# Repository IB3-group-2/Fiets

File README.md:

# Fiets

https://discord.gg/eE4hEDwp

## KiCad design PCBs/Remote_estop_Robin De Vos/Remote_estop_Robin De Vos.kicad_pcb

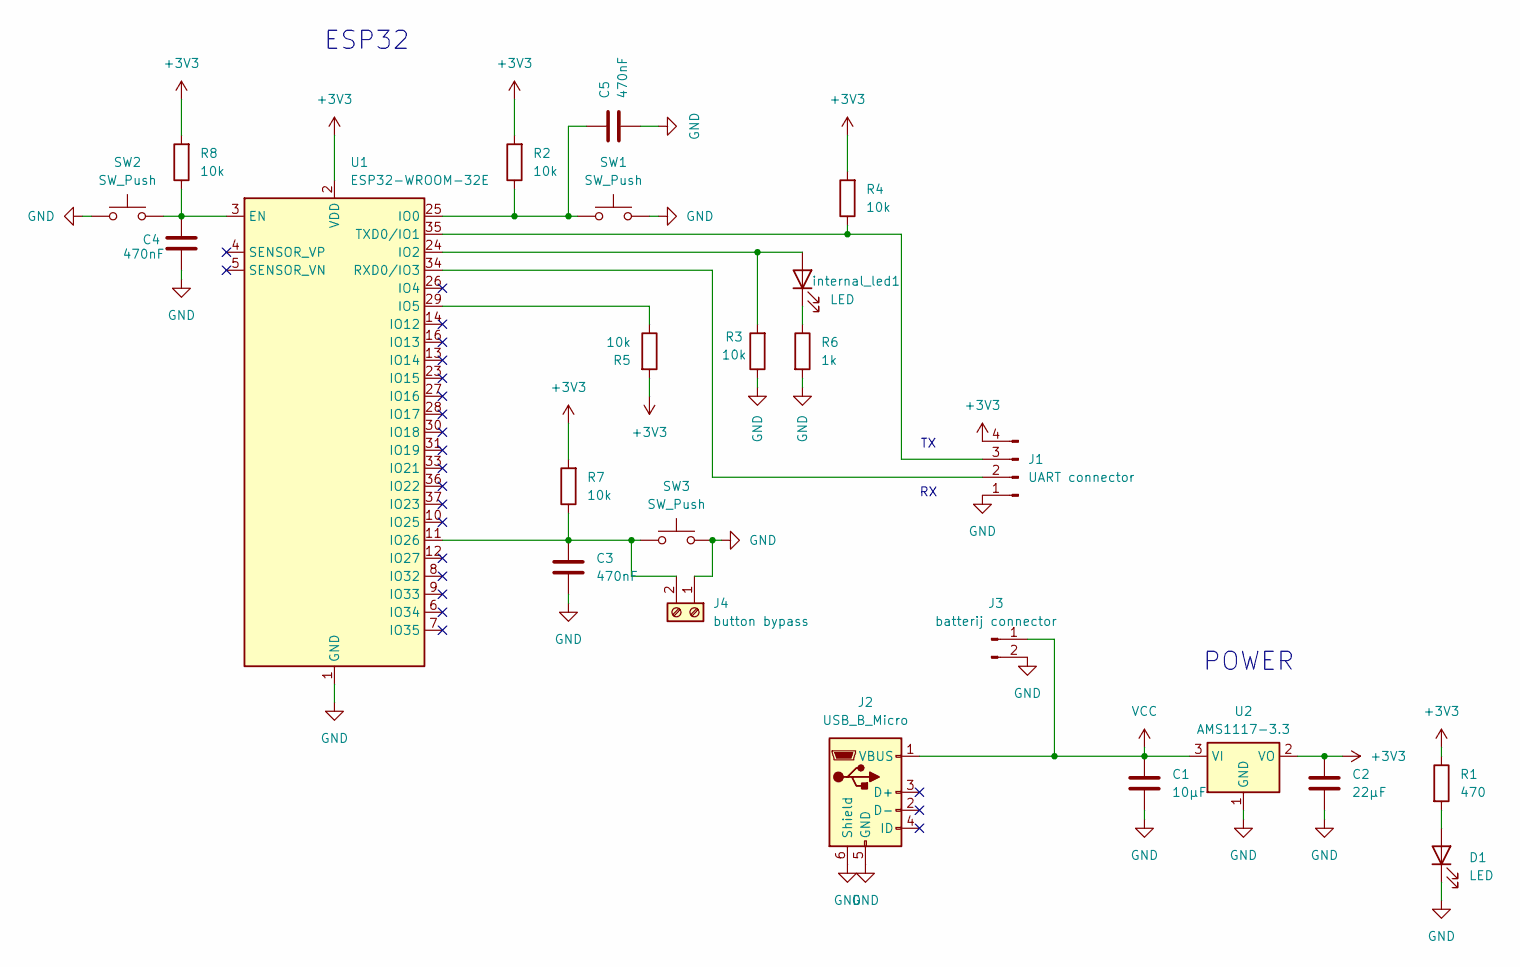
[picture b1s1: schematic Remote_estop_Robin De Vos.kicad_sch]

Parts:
C1: 10µF; C_0805_2012Metric_Pad1.18x1.45mm_HandSolder
C2: 22µF; C_0805_2012Metric_Pad1.18x1.45mm_HandSolder
C3, C4, C5: 470nF; C_0805_2012Metric_Pad1.18x1.45mm_HandSolder
D1: LED; LED_0805_2012Metric_Pad1.15x1.40mm_HandSolder
J1: UART connector; PinHeader_1x04_P2.54mm_Vertical
J2: USB_B_Micro; USB_Micro-B_Molex-105017-0001
J3: batterij connector; PinHeader_1x02_P2.54mm_Vertical
J4: button bypass; TerminalBlock_MaiXu_MX126-5.0-02P_1x02_P5.00mm
R1: 470; R_0805_2012Metric_Pad1.20x1.40mm_HandSolder
R2, R3, R4, R5, R7, R8: 10k; R_0805_2012Metric_Pad1.20x1.40mm_HandSolder
R6: 1k; R_0805_2012Metric_Pad1.20x1.40mm_HandSolder
SW1, SW2, SW3: SW_Push; 434111043826
U1: ESP32-WROOM-32E; ESP32-WROOM-32D
U2: AMS1117-3.3; SOT-223-3_TabPin2
internal_led1: LED; LED_0805_2012Metric_Pad1.15x1.40mm_HandSolder

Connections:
+3V3: C2.1, J1.4, R1.1, R2.2, R4.2, R5.2, R7.2, R8.2, U1.2 (VDD), U2.2 (VO)
GND: C1.2, C2.2, C3.2, C4.2, C5.2, D1.1 (K), J1.1, J2.5 (GND), J2.6 (Shield), J3.2, J4.1, R3.1, R6.2, SW1.2, SW2.1, SW3.2, U1.1 (GND), U1.15 (GND), U1.38 (GND), U1.39 (GND), U2.1 (GND)
unnamed: D1.2 (A), R1.2
unnamed: J1.2, U1.34 (RXD0/IO3)
unnamed: J1.3, R4.1, U1.35 (TXD0/IO1)
unnamed: C3.1, J4.2, R7.1, SW3.1, U1.11 (IO26)
unnamed: C4.1, R8.1, SW2.2, U1.3 (EN)
unnamed: C5.1, R2.1, SW1.1, U1.25 (IO0)
unnamed 8: R3.2, U1.24 (IO2), internal_led1.2 (A); also elsewhere on the board
unnamed: R5.1, U1.29 (IO5)
unnamed 10: R6.1, internal_led1.1 (K); also elsewhere on the board
VCC: C1.1, J2.1 (VBUS), J3.1, U2.3 (VI)

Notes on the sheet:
POWER
ESP32

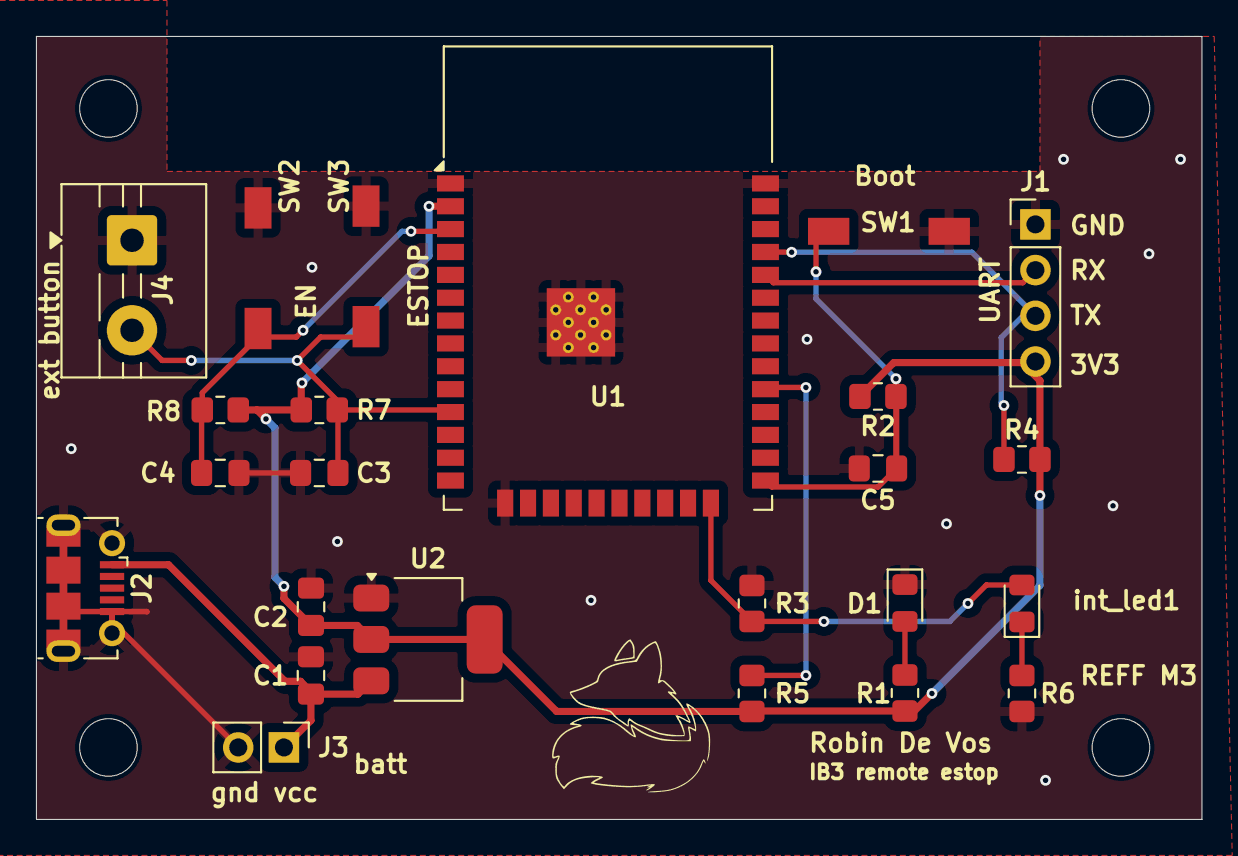
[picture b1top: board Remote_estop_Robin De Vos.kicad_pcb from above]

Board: 2 copper layers, 64.8 x 43.5 mm, 25 parts (0 on the bottom side), 12 nets.

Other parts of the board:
REFF M3: MountingHole_3.2mm_M3
int_led1: LED; LED_0805_2012Metric_Pad1.15x1.40mm_HandSolder

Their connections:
unnamed 8: int_led1.2 (A); also elsewhere on the board
unnamed 10: int_led1.1 (K); also elsewhere on the board

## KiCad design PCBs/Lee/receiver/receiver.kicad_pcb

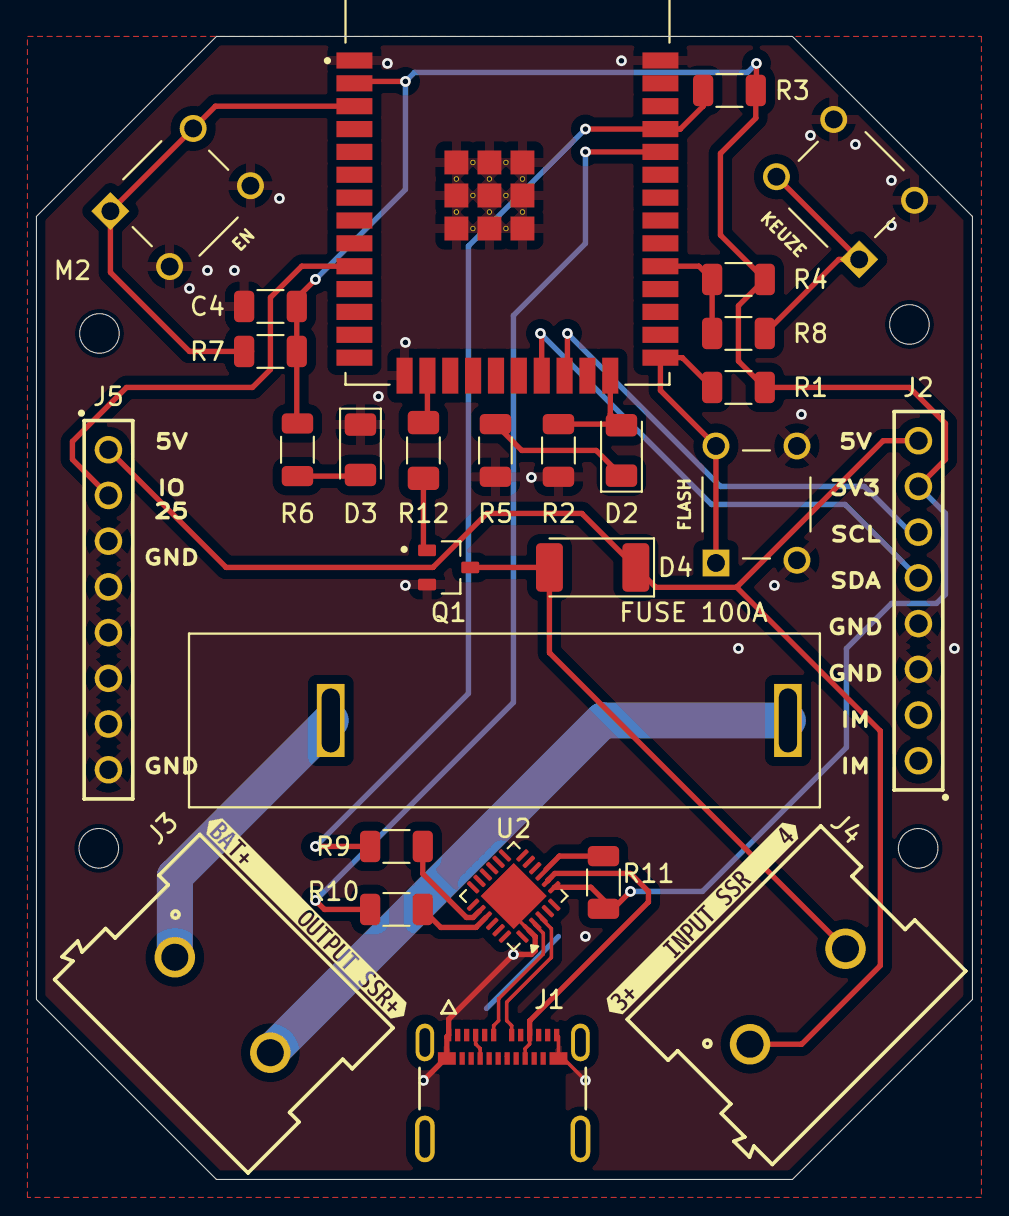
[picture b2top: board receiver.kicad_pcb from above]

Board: 2 copper layers, 52.0 x 63.5 mm, 34 parts (0 on the bottom side), 27 nets.

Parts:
C4: 100uF/6.3V; R_1206_3216Metric
D2: BLUE; LED_1206_3216Metric
D3: RED; LED_1206_3216Metric
D4: SM4007; D_MELF
EN: 3-1825910-1; TE_3-1825910-1
FLASH: 3-1825910-1; TE_3-1825910-1
FUSE 100A: Fuseholder; FUSE_3526
H2, H3, H4: MountingHole; MountingHole_2.2mm_M2
J1: 1054500101 USB-C; MOLEX_1054500101
J2: Ingangspinnen; 61300811821
J3: J3; 691253910002
J4: INPUT SSR; 691253910002
J5: motorcontroller; 61300811821
KEUZE: 3-1825910-1; TE_3-1825910-1
M2: MountingHole; MountingHole_2.2mm_M2
Q1: BC847A; TRANS_BC847A
R1, R2, R3, R4: 10k; R_1206_3216Metric
R5, R6, R9, R10: 1k; R_1206_3216Metric
R7: 10K; R_1206_3216Metric
R8: 200; R_1206_3216Metric
R11: 4.7k; R_1206_3216Metric
R12: 1k; R_1206_3216Metric_Pad1.30x1.75mm_HandSolder
U1: ESP32-WROOM-32; MODULE_ESP32-WROOM-32
U2: CP2102N; QFN-24-1EP_4x4mm_P0.5mm_EP2.6x2.6mm
kibuzzard-69131E5B: G***; kibuzzard-69131E5B
kibuzzard-69131EBA: G***; kibuzzard-69131EBA

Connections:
5V: D4.1 (K), J2.8, J4.1, J5.1
/BAT +: FUSE 100A.1, J3.1
/INPUT SSR 4: D4.2 (A), J4.2, Q1.3
/OUTPUT SSR +: FUSE 100A.2, J3.2
D+: J1.A6 (D1+), U2.3 (D+)
D-: J1.A7 (D1-), U2.4 (D-)
EN: EN.1, EN.2, R7.2, U1.3 (EN)
GND: C4.2, D3.1 (K), EN.3, EN.4, FLASH.3, FLASH.4, J1.A1 (GND_A1), J1.A12 (GND_A12), J1.B1 (GND_B1), J1.B12 (GND_B12), J2.3, J2.4, J5.3, J5.4, J5.5, J5.6, J5.7, J5.8, KEUZE.3, KEUZE.4, Q1.2, R2.1, R5.2, U1.1 (GND), U1.15 (GND), U1.38 (GND), U1.39_1 (GND), U1.39_2 (GND), U1.39_3 (GND), U1.39_4 (GND), U1.39_5 (GND), U1.39_6 (GND), U1.39_7 (GND), U1.39_8 (GND), U1.39_9 (GND), U1.39_10 (GND), U1.39_11 (GND), U1.39_12 (GND), U1.39_13 (GND), U1.39_14 (GND), U1.39_15 (GND), U1.39_16 (GND), U1.39_17 (GND), U1.39_18 (GND), U1.39_19 (GND), U1.39_20 (GND), U1.39_21 (GND), U2.2 (GND), U2.25 (GND)
GPIO0: FLASH.1, FLASH.2, R1.2, U1.25 (IO0)
GPIO2: D2.2 (A), R2.2, U1.24 (IO2)
GPIO5: R4.2, R8.1, U1.29 (IO5)
GPIO13: R12.1, U1.16 (IO13)
GPIO25: J5.2, U1.10 (IO25)
Imeasure: J2.1, J2.2
unnamed: D2.1 (K), R5.1
unnamed: D3.2 (A), R6.2
unnamed: KEUZE.1, KEUZE.2, R8.2
unnamed: Q1.1, R12.2
unnamed: R9.1, U2.20 (RXD)
unnamed: R10.1, U2.21 (TXD)
unnamed: R11.2, U2.9 (~RST)
RX0: R10.2, U1.34 (RXD0)
SCL: J2.6, U1.22 (SDI/SD1)
SDA: J2.5, U1.21 (SDO/SD0)
TX0: R3.2, R9.2, U1.35 (TXD0)
VCCUSB: J1.A4 (VBUS_A4), J1.A9 (VBUS_A9), J1.B4 (VBUS_B4), J1.B9 (VBUS_B9), U2.8 (VBUS)
VDD3V3: C4.1, J2.7, R1.1, R3.1, R4.1, R6.1, R7.1, R11.1, U1.2 (3V3), U2.6 (VDD), U2.7 (VREGIN)

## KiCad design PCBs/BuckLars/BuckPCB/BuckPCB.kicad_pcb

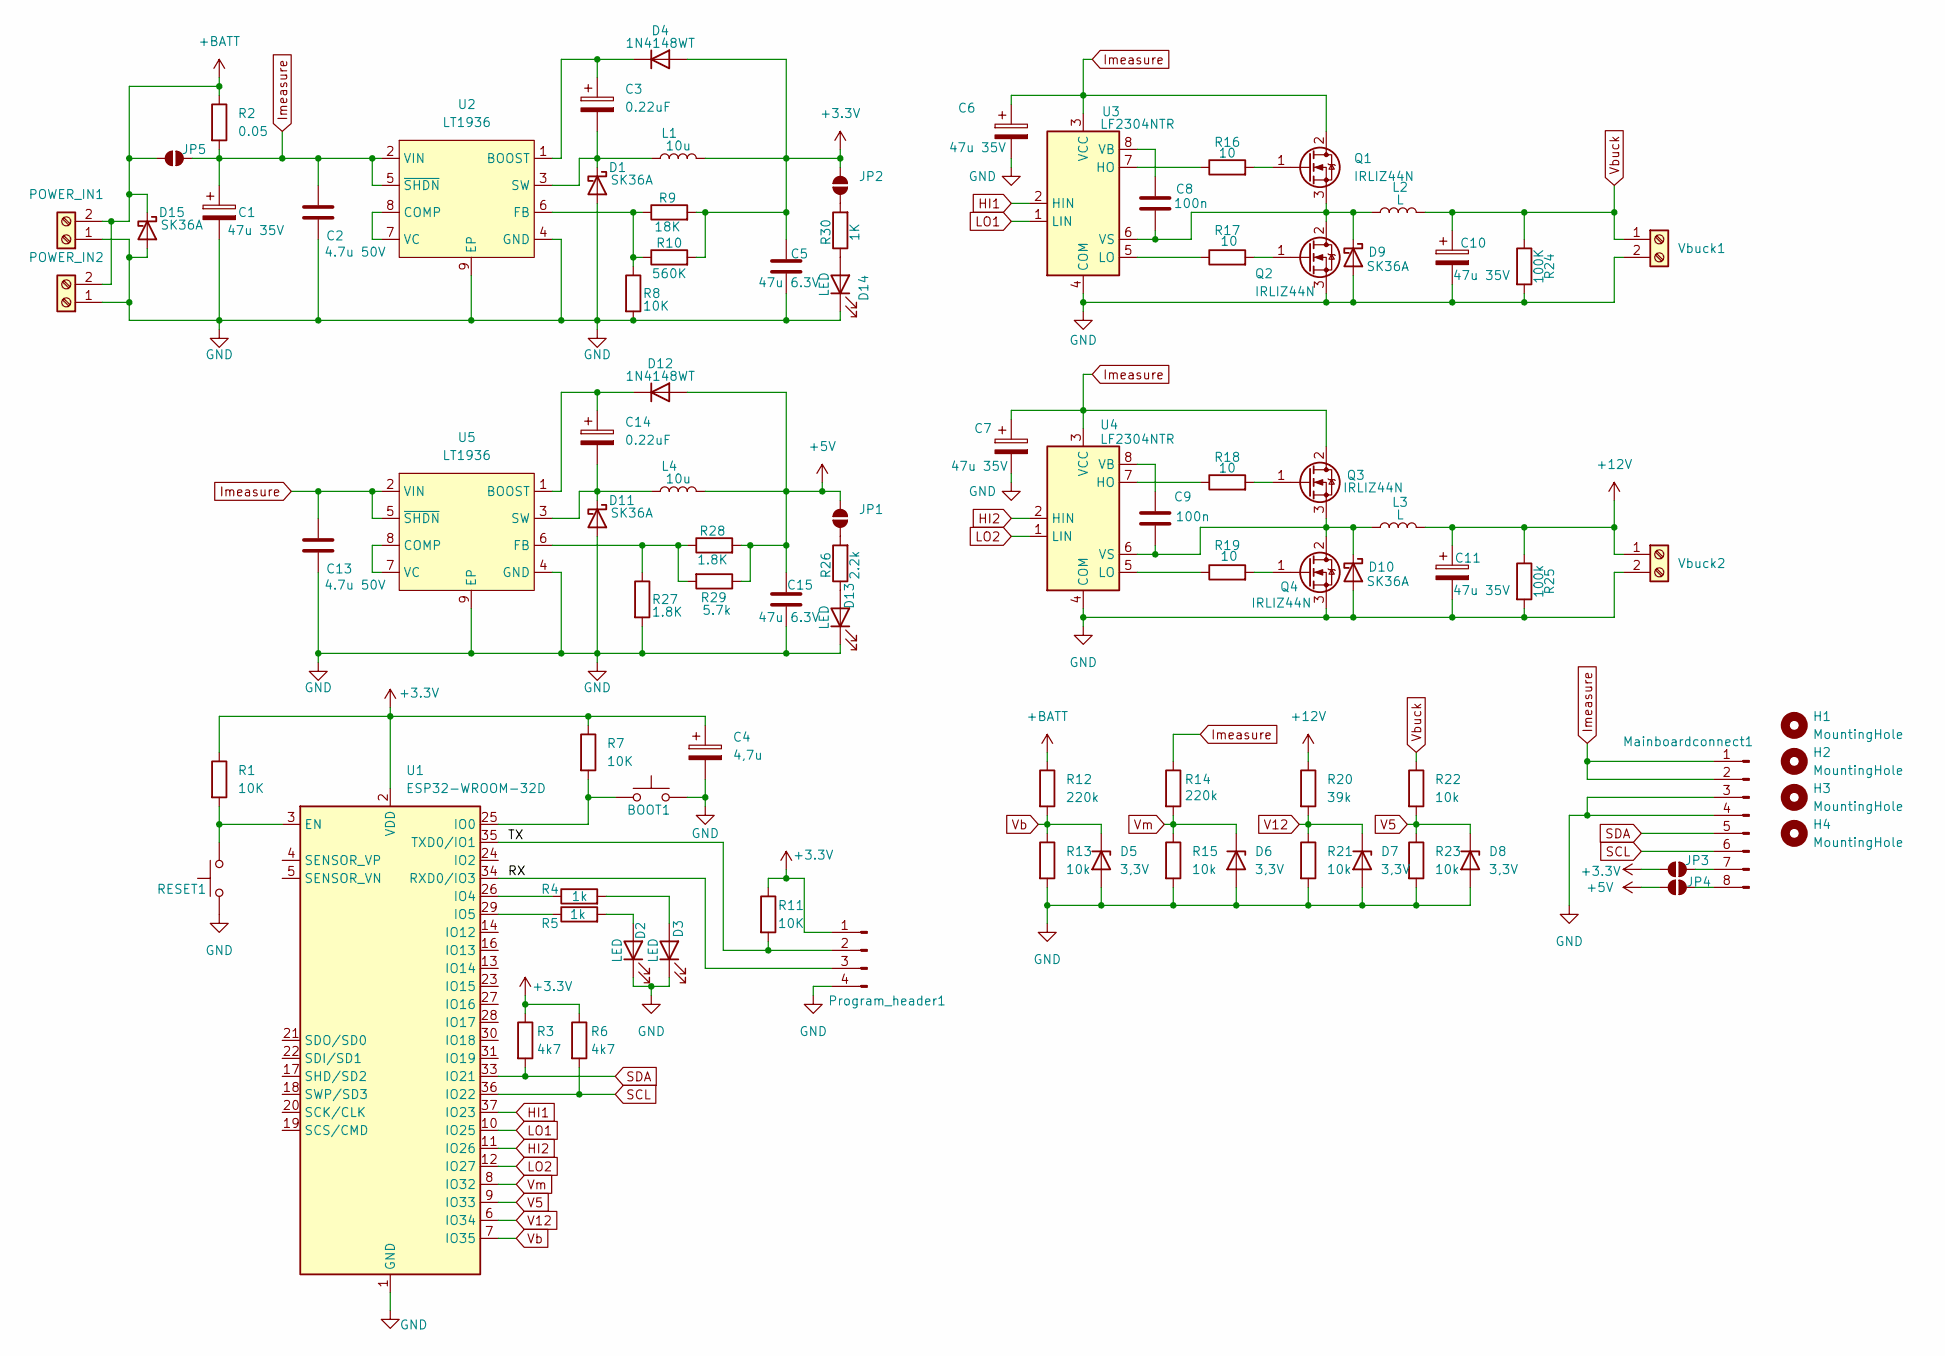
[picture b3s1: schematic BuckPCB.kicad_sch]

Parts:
BOOT1: BOOT; SW_Tactile_SPST_NO_Straight_CK_PTS636Sx25SMTRLFS
C1, C6, C7, C10, C11: 47u 35V; CP_Elec_6.3x5.7
C2, C13: 4.7u 50V; D_1206_3216Metric_Pad1.42x1.75mm_HandSolder
C3, C14: 0.22uF; C_1206_3216Metric_Pad1.33x1.80mm_HandSolder
C4: 4,7u; CP_Elec_4x5.3
C5, C15: 47u 6.3V; D_1206_3216Metric_Pad1.42x1.75mm_HandSolder
C8, C9: 100n; C_1206_3216Metric_Pad1.33x1.80mm_HandSolder
D1, D9, D10, D11, D15: SK36A; D_SMC-RM10_Universal_Handsoldering
D2, D3, D13, D14: LED; LED_0805_2012Metric
D4, D12: 1N4148WT; D_SOD-523
D5, D6, D7, D8: 3,3V; D_1206_3216Metric
H1, H2, H3, H4: MountingHole; MountingHole_3.2mm_M3_ISO14580
JP1, JP2, JP3, JP4, JP5: SolderJumper_2_Open; SolderJumper-2_P1.3mm_Open_TrianglePad1.0x1.5mm
L1, L4: 10u; L_7.3x7.3_H4.5
L2, L3: L; L_7.3x7.3_H4.5
Mainboardconnect1: Conn_01x08_Pin; PinHeader_1x08_P2.54mm_Vertical
POWER_IN1, POWER_IN2: POWER_IN; TerminalBlock_MaiXu_MX126-5.0-02P_1x02_P5.00mm
Program_header1: Program_header; PinHeader_1x04_P2.54mm_Vertical
Q1, Q2, Q3, Q4: IRLIZ44N; TO-220F-3_Vertical
R1, R7, R8, R11: 10K; R_1206_3216Metric_Pad1.30x1.75mm_HandSolder
R2: 0.05; R_4020_10251Metric_Pad1.65x5.30mm_HandSolder
R3, R6: 4k7; R_1206_3216Metric_Pad1.30x1.75mm_HandSolder
R4, R5: 1k; R_1206_3216Metric_Pad1.30x1.75mm_HandSolder
R9: 18K; R_1206_3216Metric_Pad1.30x1.75mm_HandSolder
R10: 560K; R_1206_3216Metric_Pad1.30x1.75mm_HandSolder
R12, R14: 220k; R_1206_3216Metric_Pad1.30x1.75mm_HandSolder
R13, R15, R21, R22, R23: 10k; R_1206_3216Metric_Pad1.30x1.75mm_HandSolder
R16, R17, R18, R19: 10; R_1206_3216Metric_Pad1.30x1.75mm_HandSolder
R20: 39k; R_1206_3216Metric_Pad1.30x1.75mm_HandSolder
R24: 100K; R_1206_3216Metric_Pad1.30x1.75mm_HandSolder
R25: 100k; R_1206_3216Metric_Pad1.30x1.75mm_HandSolder
R26: 2.2k; R_1206_3216Metric_Pad1.30x1.75mm_HandSolder
R27, R28: 1.8K; R_1206_3216Metric_Pad1.30x1.75mm_HandSolder
R29: 5.7k; R_1206_3216Metric_Pad1.30x1.75mm_HandSolder
R30: 1K; R_1206_3216Metric_Pad1.30x1.75mm_HandSolder
RESET1: RESET; SW_Tactile_SPST_NO_Straight_CK_PTS636Sx25SMTRLFS
U1: ESP32-WROOM-32D
U2, U5: LT1936; MSOP-8-1EP_3x3mm_P0.65mm_EP1.95x2.15mm
U3, U4: LF2304NTR; SOIC-8_3.9x4.9mm_P1.27mm
Vbuck1: Vbuck; TerminalBlock_MaiXu_MX126-5.0-02P_1x02_P5.00mm
Vbuck2: 12V; TerminalBlock_MaiXu_MX126-5.0-02P_1x02_P5.00mm

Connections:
+3.3V: C4.1, C5.1, D4.2 (A), JP2.2 (B), JP3.2 (B), L1.2, Program_header1.1, R1.1, R3.1, R6.1, R7.1, R9.2, R10.2, R11.1, U1.2 (VDD)
+5V: C15.1, D12.2 (A), JP1.2 (B), JP4.2 (B), L4.2, R28.2, R29.1
+12V: C11.1, L3.2, R20.1, R25.1, Vbuck2.1
+BATT: D15.1 (K), JP5.2 (B), POWER_IN1.2, POWER_IN2.2, R2.1, R12.1; also elsewhere on the board
/RX: Program_header1.3, U1.34 (RXD0/IO3)
/TX: Program_header1.2, R11.2, U1.35 (TXD0/IO1)
GND: BOOT1.2 (B), C1.2, C2.2, C4.2, C5.2, C6.2, C7.2, C10.2, C11.2, C13.2, C15.2, D1.2 (A), D2.1 (K), D3.1 (K), D5.2 (A), D6.2 (A), D7.2 (A), D8.2 (A), D9.2 (A), D10.2 (A), D11.2 (A), D13.1 (K), D14.1 (K), D15.2 (A), Mainboardconnect1.3, Mainboardconnect1.4, POWER_IN1.1, POWER_IN2.1, Program_header1.4, Q2.3 (S), Q4.3 (S), R8.2, R13.2, R15.2, R21.2, R23.2, R24.2, R25.2, R27.2, RESET1.1 (A), U1.1 (GND), U1.15 (GND), U1.38 (GND), U1.39 (GND), U2.4 (GND), U2.9 (EP), U3.4 (COM), U4.4 (COM), U5.4 (GND), U5.9 (EP), Vbuck1.2, Vbuck2.2
HI1: U1.37 (IO23), U3.2 (HIN)
HI2: U1.11 (IO26), U4.2 (HIN)
Imeasure: C1.1, C2.1, C6.1, C7.1, C13.1, JP5.1 (A), Mainboardconnect1.1, Mainboardconnect1.2, Q1.2 (D), Q3.2 (D), R2.2, R14.1, U2.2 (VIN), U2.5 (~SHDN), U3.3 (VCC), U4.3 (VCC), U5.2 (VIN), U5.5 (~SHDN); also elsewhere on the board
LO1: U1.10 (IO25), U3.1 (LIN)
LO2: U1.12 (IO27), U4.1 (LIN)
unnamed: BOOT1.1 (A), R7.2, U1.25 (IO0)
unnamed: C3.2, D1.1 (K), L1.1, U2.3 (SW)
unnamed: D2.2 (A), R5.2
unnamed: D3.2 (A), R4.2
unnamed: C3.1, D4.1 (K), U2.1 (BOOST)
unnamed: C8.2, D9.1 (K), L2.1, Q1.3 (S), Q2.2 (D), U3.6 (VS)
unnamed: C9.2, D10.1 (K), L3.1, Q3.3 (S), Q4.2 (D), U4.6 (VS)
unnamed: C14.2, D11.1 (K), L4.1, U5.3 (SW)
unnamed: C14.1, D12.1 (K), U5.1 (BOOST)
unnamed: D13.2 (A), R26.1
unnamed: D14.2 (A), R30.1
unnamed: JP1.1 (A), R26.2
unnamed: JP2.1 (A), R30.2
unnamed: JP3.1 (A), Mainboardconnect1.7
unnamed: JP4.1 (A), Mainboardconnect1.8
unnamed: Q1.1 (G), R16.2
unnamed: Q2.1 (G), R17.2
unnamed: Q3.1 (G), R18.2
unnamed: Q4.1 (G), R19.2
unnamed: R1.2, RESET1.2 (B), U1.3 (EN)
unnamed: R4.1, U1.26 (IO4)
unnamed: R5.1, U1.29 (IO5)
unnamed: U2.7 (VC), U2.8 (COMP)
unnamed: R8.1, R9.1, R10.1, U2.6 (FB)
unnamed: R16.1, U3.7 (HO)
unnamed: R17.1, U3.5 (LO)
unnamed: C8.1, U3.8 (VB)
unnamed: R18.1, U4.7 (HO)
unnamed: R19.1, U4.5 (LO)
unnamed: C9.1, U4.8 (VB)
unnamed: U5.7 (VC), U5.8 (COMP)
unnamed: R27.1, R28.1, R29.2, U5.6 (FB)
SCL: Mainboardconnect1.6, R6.2, U1.36 (IO22)
SDA: Mainboardconnect1.5, R3.2, U1.33 (IO21)
V5: D8.1 (K), R22.2, R23.1, U1.9 (IO33)
V12: D7.1 (K), R20.2, R21.1, U1.6 (IO34)
Vb: D5.1 (K), R12.2, R13.1, U1.7 (IO35)
Vbuck: C10.1, L2.2, R22.1, R24.1, Vbuck1.1
Vm: D6.1 (K), R14.2, R15.1, U1.8 (IO32)

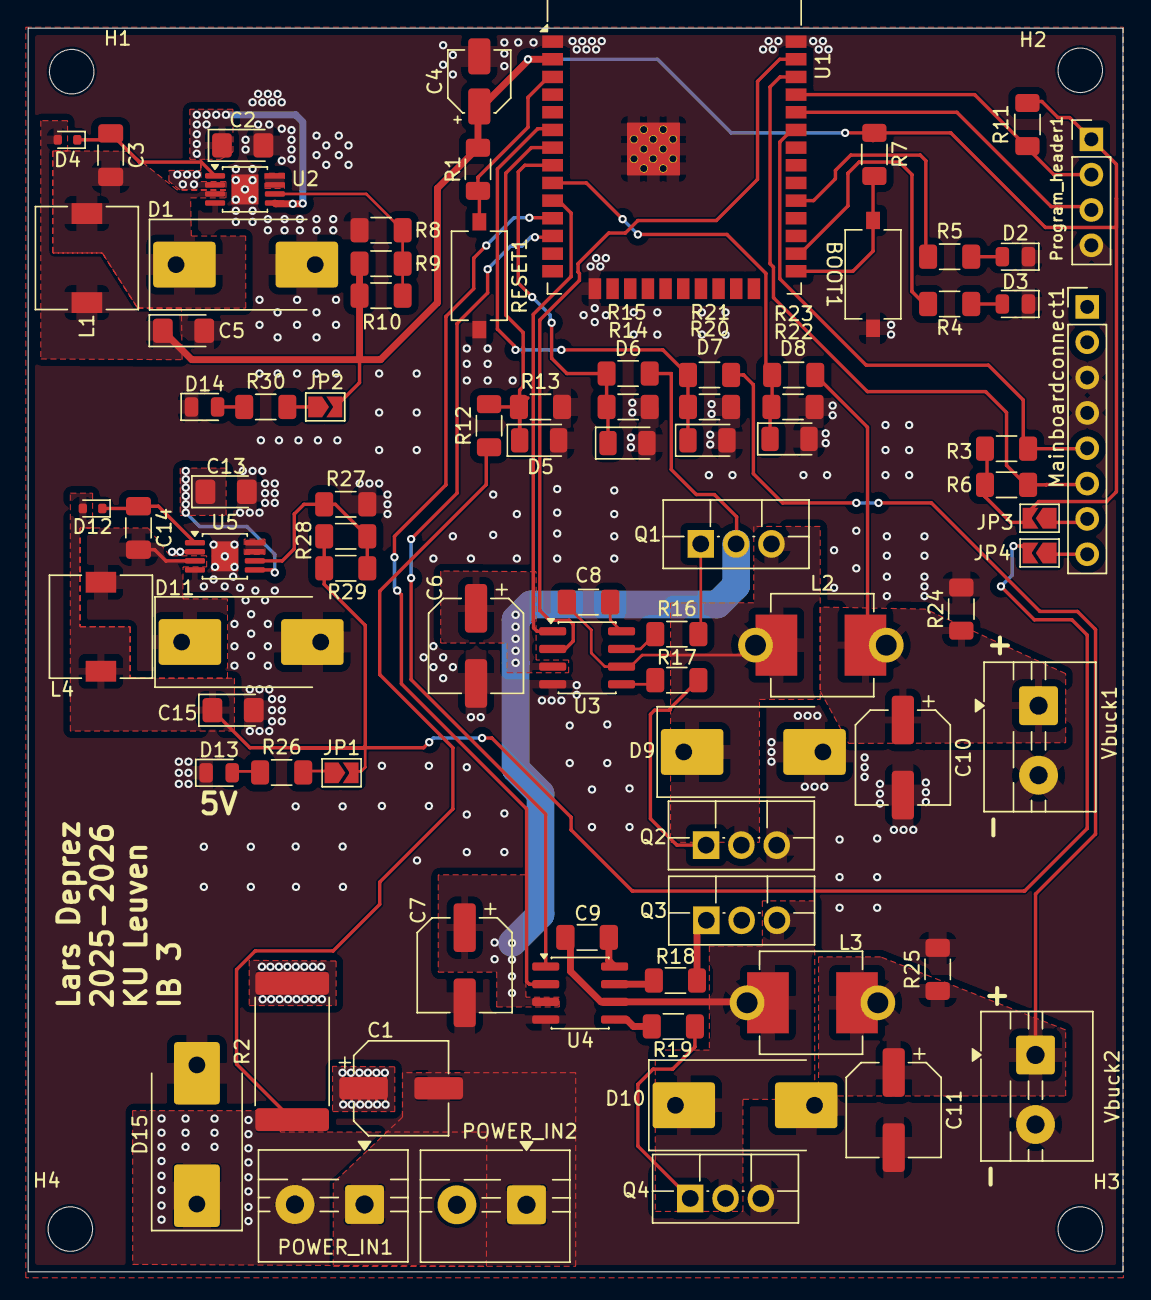
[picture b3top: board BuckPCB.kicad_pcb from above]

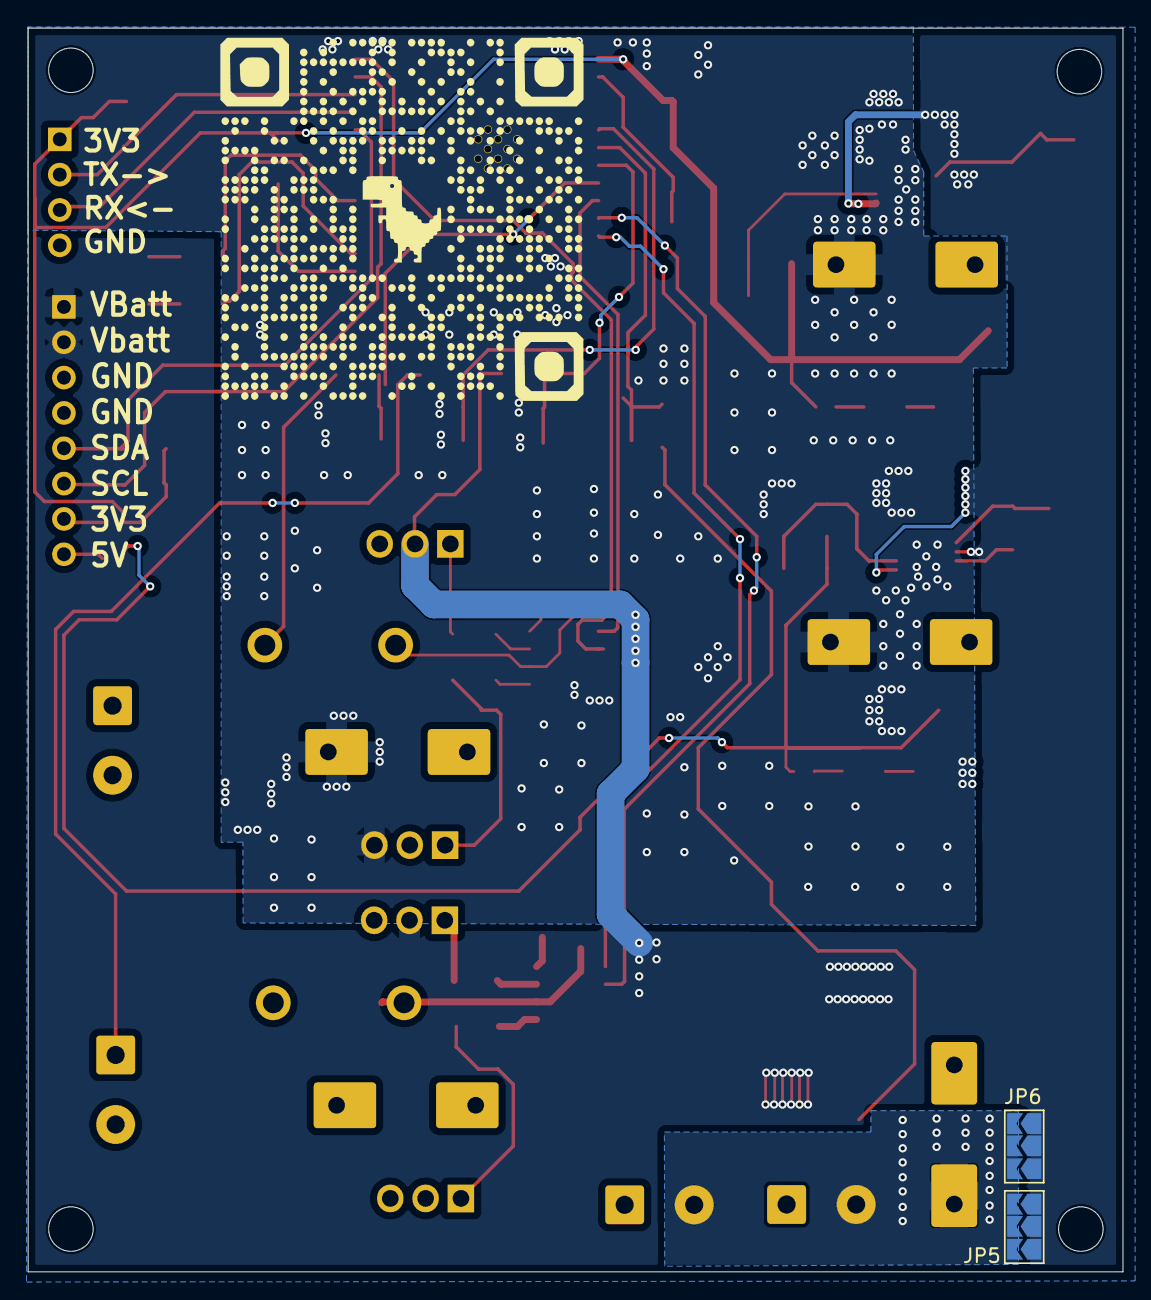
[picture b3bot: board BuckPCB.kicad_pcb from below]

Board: 2 copper layers, 78.7 x 89.4 mm, 90 parts (2 on the bottom side), 51 nets.

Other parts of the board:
JP6: SolderJumper_2_Open; SolderJumper-2_P1.3mm_Open_TrianglePad1.0x1.5mm

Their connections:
+BATT: JP6.2 (B); also elsewhere on the board
Imeasure: JP6.1 (A); also elsewhere on the board

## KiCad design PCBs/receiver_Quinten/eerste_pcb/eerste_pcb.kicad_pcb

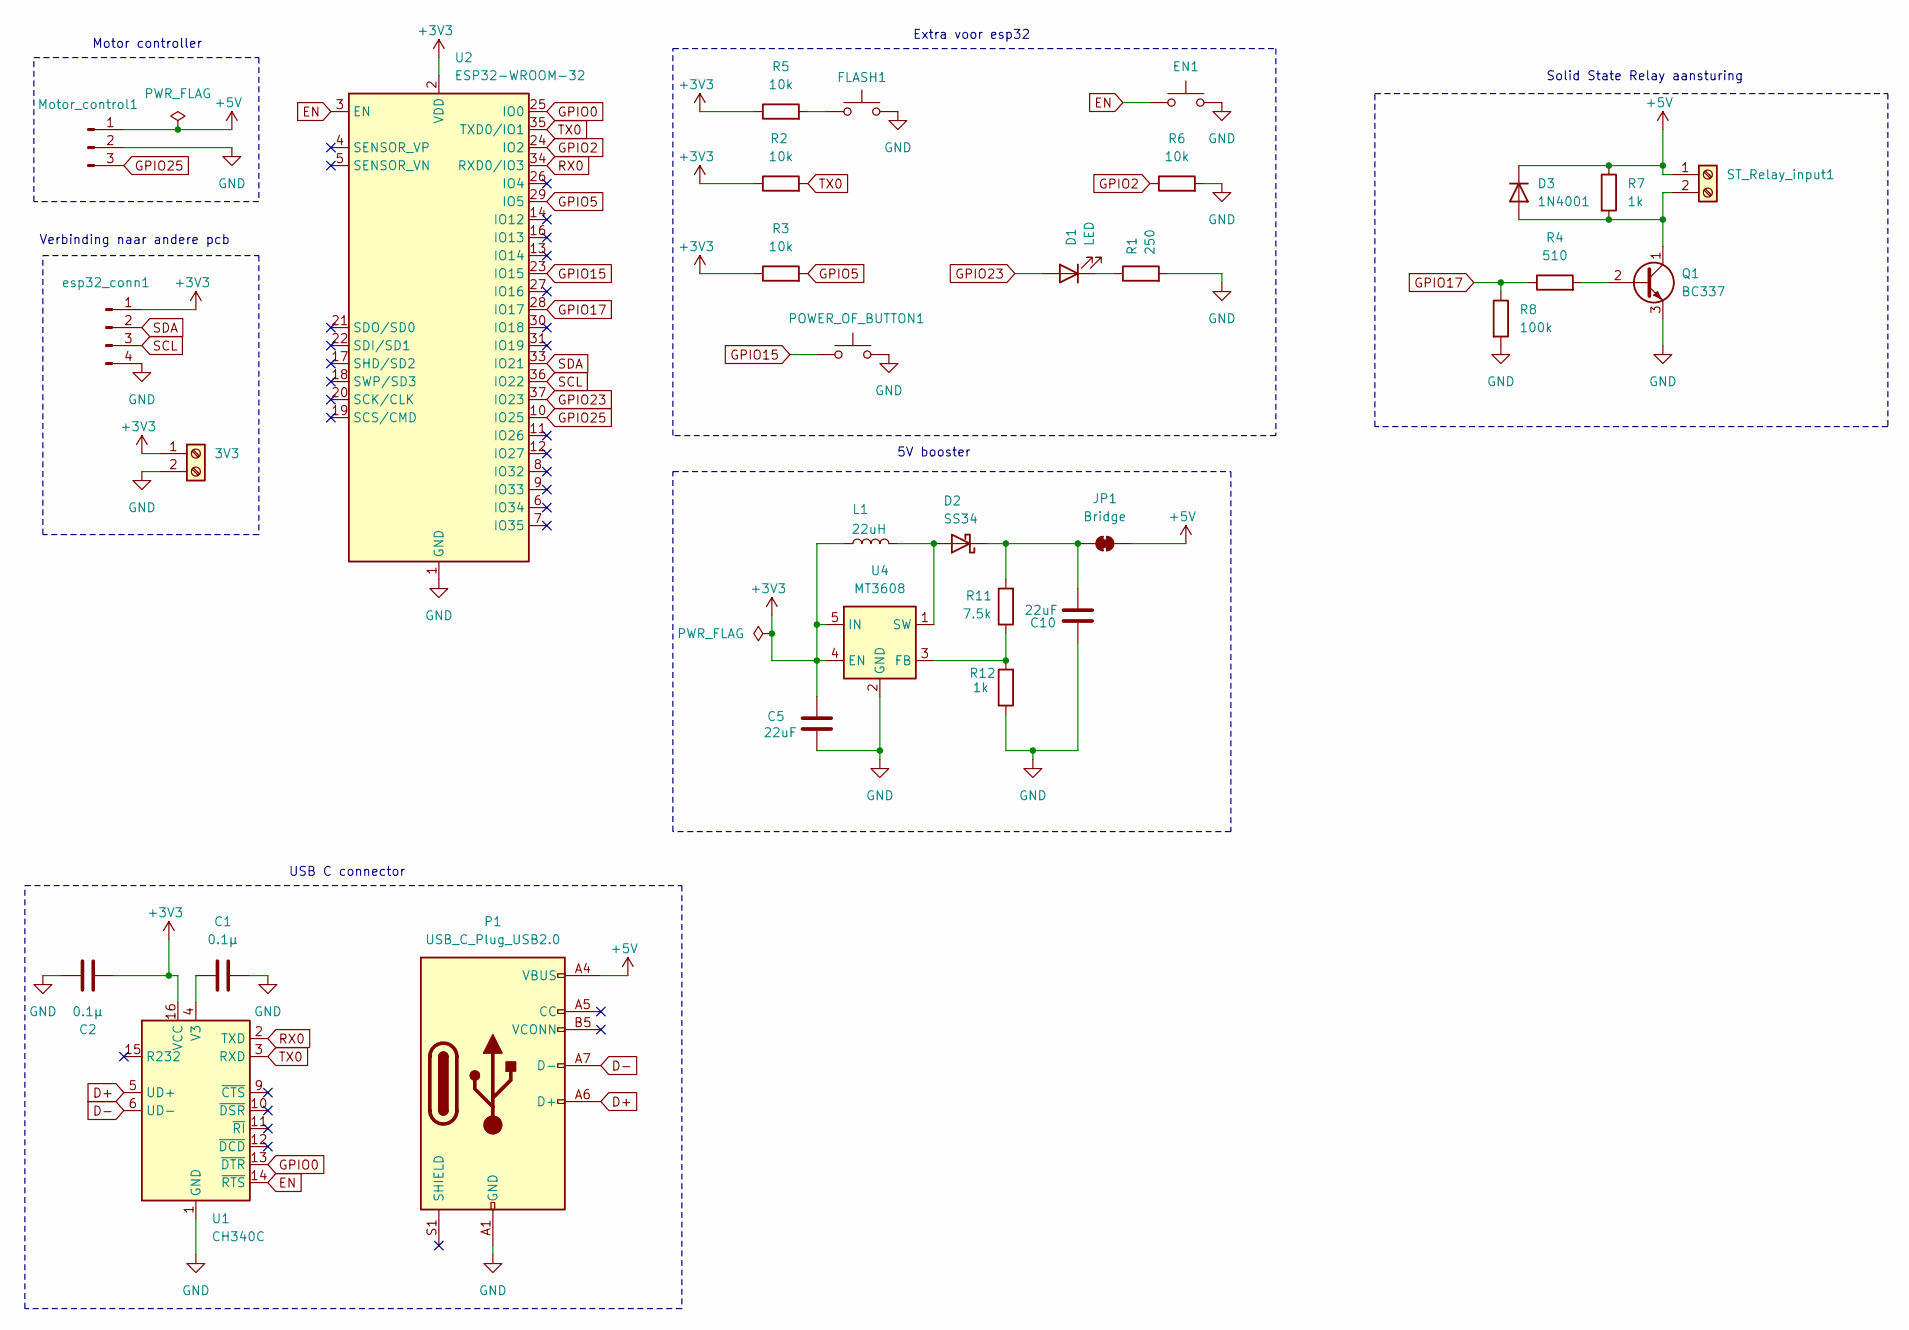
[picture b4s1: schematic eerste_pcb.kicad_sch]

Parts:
3V3: JST_SFH_SM02B-SFHRS-TF_1x02-1MP_P4.20mm_Horizontal
C1, C2: 0.1µ; C_1206_3216Metric_Pad1.33x1.80mm_HandSolder
C5, C10: 22uF; C_1206_3216Metric_Pad1.33x1.80mm_HandSolder
D1: LED; LED_1210_3225Metric_Pad1.42x2.65mm_HandSolder
D2: SS34; D_SMA
D3: 1N4001; SOT-23
EN1: EN; SW_PUSH_6mm
FLASH1: FLASH; SW_PUSH_6mm
JP1: Bridge; SolderJumper-2_P1.3mm_Bridged2Bar_Pad1.0x1.5mm
L1: 22uH; L_Bourns_SRP7028A_7.3x6.6mm
Motor_control1: Conn_01x03_Pin; PinHeader_1x03_P2.54mm_Vertical
P1: USB_C_Plug_USB2.0; USB_C_Receptacle_JAE_DX07S024WJ3R400
POWER_OF_BUTTON1: POWER OF BUTTON; SW_PUSH_6mm
Q1: BC337; TO-92_Inline
R1: 250; R_0805_2012Metric
R2, R3, R5, R6: 10k; R_1206_3216Metric_Pad1.30x1.75mm_HandSolder
R4: 510; R_1206_3216Metric_Pad1.30x1.75mm_HandSolder
R7, R12: 1k; R_1206_3216Metric_Pad1.30x1.75mm_HandSolder
R8: 100k; R_1206_3216Metric_Pad1.30x1.75mm_HandSolder
R11: 7.5k; R_1206_3216Metric_Pad1.30x1.75mm_HandSolder
ST_Relay_input1: ST_Relay_input1; JST_SFH_SM02B-SFHRS-TF_1x02-1MP_P4.20mm_Horizontal
U1: CH340C; SOIC-16_3.9x9.9mm_P1.27mm
U2: ESP32-WROOM-32
U4: MT3608; SOT-23-6
esp32_conn1: Conn_01x04_Pin; PinHeader_1x04_P2.54mm_Vertical

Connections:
+3V3: 3V3.1, C2.1, C5.1, L1.1, R2.1, R3.1, R5.1, U1.16 (VCC), U2.2 (VDD), U4.4 (EN), U4.5 (IN), esp32_conn1.1
+5V: D3.1 (K), JP1.2 (B), Motor_control1.1, P1.A4 (VBUS), P1.A9 (VBUS), P1.B4 (VBUS), P1.B9 (VBUS), R7.1, ST_Relay_input1.1
D+: P1.A6 (D+), U1.5 (UD+)
D-: P1.A7 (D-), U1.6 (UD-)
EN: EN1.1, U1.14 (~RTS), U2.3 (EN)
GND: 3V3.2, C1.2, C2.2, C5.2, C10.2, EN1.2, FLASH1.2, Motor_control1.2, P1.A1 (GND), P1.A12 (GND), P1.B1 (GND), P1.B12 (GND), POWER_OF_BUTTON1.2, Q1.3 (E), R1.2, R6.2, R8.2, R12.1, U1.1 (GND), U2.1 (GND), U2.15 (GND), U2.38 (GND), U2.39 (GND), U4.2 (GND), esp32_conn1.4
GPIO0: U1.13 (~DTR), U2.25 (IO0)
GPIO2: R6.1, U2.24 (IO2)
GPIO5: R3.2, U2.29 (IO5)
GPIO15: POWER_OF_BUTTON1.1, U2.23 (IO15)
GPIO17: R4.1, R8.1, U2.28 (IO17)
GPIO23: D1.2 (A), U2.37 (IO23)
GPIO25: Motor_control1.3, U2.10 (IO25)
unnamed: D1.1 (K), R1.1
unnamed: D2.2 (A), L1.2, U4.1 (SW)
unnamed: C10.1, D2.1 (K), JP1.1 (A), R11.2
unnamed: D3.2 (A), Q1.1 (C), R7.2, ST_Relay_input1.2
unnamed: FLASH1.1, R5.2
unnamed: Q1.2 (B), R4.2
unnamed: C1.1, U1.4 (V3)
unnamed: R11.1, R12.2, U4.3 (FB)
RX0: U1.2 (TXD), U2.34 (RXD0/IO3)
SCL: U2.36 (IO22), esp32_conn1.3
SDA: U2.33 (IO21), esp32_conn1.2
TX0: R2.2, U1.3 (RXD), U2.35 (TXD0/IO1)

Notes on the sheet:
Verbinding naar andere pcb
5V booster
Motor controller
Solid State Relay aansturing
Extra voor esp32
USB C connector

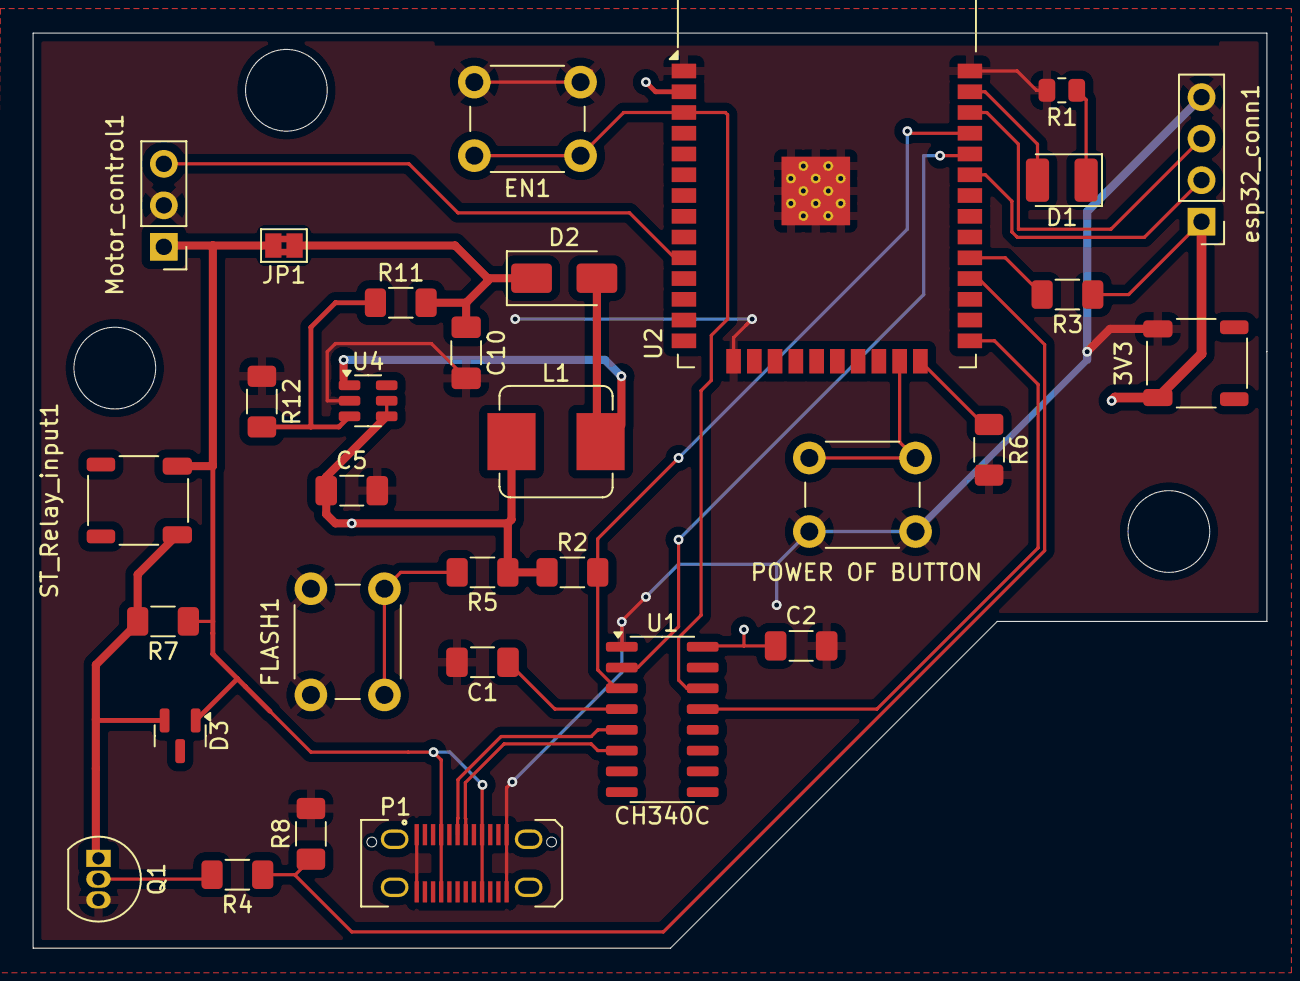
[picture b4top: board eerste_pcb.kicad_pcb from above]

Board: 2 copper layers, 75.5 x 56.0 mm, 31 parts (0 on the bottom side), 25 nets.
